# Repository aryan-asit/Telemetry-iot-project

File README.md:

# 4-Layer IoT Telemetry Board

A custom 4-layer IoT Telemetry Board designed from scratch using KiCad. The board is built around an ESP32 and integrates environmental sensing, local data storage, USB connectivity, wireless communication, and battery charging and power management in a compact PCB.

## Project Overview

The goal of this project was to design a compact and reliable IoT hardware platform capable of collecting environmental data, processing it locally, storing telemetry data, and communicating wirelessly.

The project covers the complete PCB development workflow, from component selection and schematic design to PCB layout, verification, 3D inspection, and manufacturing file generation.

## 3D PCB View

## Key Features

### ESP32 Processing and Connectivity

The ESP32 is the main controller of the board and provides:

- Sensor data acquisition
- Local data processing
- Wi-Fi connectivity
- Bluetooth connectivity
- Communication with external peripherals

### Sensors

The board includes multiple sensing elements for environmental and acoustic monitoring:

- Microphone for sound sensing
- Humidity sensor for environmental monitoring
- Ambient light sensor for light-level measurement

### Data Storage

Two storage options are integrated into the board:

- Micro SD card for removable and higher-capacity data storage
- Flash memory for local non-volatile storage

### Power Management

The power section is based on the MCP73871 battery charging and power-management IC.

Main power features include:

- USB Type-C power input
- Battery charging
- Power-path management
- Battery-powered operation
- Dedicated 3.3 V regulation using an LM1117-3.3V regulator

### USB Type-C

A USB Type-C connector is included for power input and USB communication.

## PCB Stack-Up

The board uses a 4-layer PCB stack-up to improve power distribution, grounding, and routing flexibility.

| Layer | Purpose |
|---|---|
| Layer 1 | Signal |
| Layer 2 | Ground Plane |
| Layer 3 | Power Plane - 5 V and 3.3 V zones |
| Layer 4 | Signal |

The dedicated ground and power layers provide continuous return paths and simplify power distribution across the board.

## Communication Interfaces

| Interface | Purpose |
|---|---|
| I2C | Sensor and peripheral communication |
| SPI | SD card, flash memory, and other peripherals |
| USB | Power, programming, and communication |
| Wi-Fi | Wireless connectivity |
| Bluetooth | Short-range wireless connectivity |

## System Architecture

```text
                         +---------------------+
                         |     USB Type-C      |
                         |    Power / USB      |
                         +----------+----------+
                                    |
                                    v
                         +---------------------+
                         |      MCP73871       |
                         | Battery Charging &  |
                         |   Power Management  |
                         +----------+----------+
                                    |
                                    v
                         +---------------------+
                         |     LM1117-3.3V     |
                         |  Voltage Regulation |
                         +----------+----------+
                                    |
                                    v
                    +------------------------------+
                    |             ESP32            |
                    |      Processing & Control    |
                    |                              |
                    |       Wi-Fi + Bluetooth     |
                    +--------+----------+----------+
                             |          |
                 +-----------+----------+-----------+
                 |                      |           |
                 v                      v           v
          +-------------+       +-------------+ +---------+
          |   Sensors   |       |   Storage   | |  USB    |
          |             |       |             | | Type-C  |
          | Microphone  |       | Micro SD    | |         |
          | Humidity    |       | Flash       | |         |
          | Light       |       |             | |         |
          +-------------+       +-------------+ +---------+
```

## PCB Design Workflow

### 1. Concept Development

Defined the requirements for a compact IoT telemetry platform covering sensing, processing, storage, communication, and power management.

### 2. Component Selection

Selected the ESP32, sensors, memory devices, charging IC, regulator, connectors, and supporting components based on the system requirements.

### 3. Schematic Design

Designed and reviewed the complete circuit schematic and connected the individual functional blocks.

### 4. Footprint Selection and Creation

Selected suitable KiCad footprints and created or customized footprints where required.

### 5. PCB Layout

Defined the 4-layer stack-up and placed components while considering board size, routing complexity, signal paths, power distribution, and component accessibility.

### 6. Routing

Routed signal, power, and communication connections with attention to return paths, grounding, and clean power distribution.

### 7. 3D Verification

Configured 3D models and inspected the complete board to verify component placement and the overall physical arrangement.

### 8. ERC and DRC Verification

Performed Electrical Rules Check (ERC) and Design Rules Check (DRC) to identify and resolve schematic and PCB design issues.

### 9. Manufacturing Output

Generated Gerber and other required manufacturing files for PCB fabrication.

## Design Highlights

### 4-Layer PCB Design

The dedicated ground and power layers provide better power distribution and more flexible signal routing than a basic 2-layer approach.

### Integrated Power Management

The MCP73871 handles battery charging and power-path management, while the LM1117-3.3V provides a regulated 3.3 V supply for the low-voltage circuitry.

### Multiple Peripheral Interfaces

The board combines sensors, storage, USB, and wireless communication on a single PCB, making it suitable for different embedded and IoT applications.

### Compact Functional Layout

The component placement and routing were optimized to balance board size, functionality, accessibility, and routing complexity.

## Repository Contents

```text
Telemetry-iot-project/
|
+-- IOT_PCB/
|   +-- KiCad schematic and PCB design files
|
+-- images/
|   +-- telemetry-board-3d.png
|
+-- schematic files.pdf
|   +-- Complete schematic documentation
|
+-- Screenshot *.png
|   +-- PCB design and layout screenshots
|
+-- README.md
|   +-- Project documentation
```

## Tools and Technologies

### Hardware

- ESP32
- Microphone
- Humidity sensor
- Ambient light sensor
- Micro SD card
- Flash memory
- MCP73871
- LM1117-3.3V
- USB Type-C

### PCB Design

- KiCad v10
- Schematic Capture
- PCB Layout
- Footprint and Symbol Management
- 3D PCB Visualization
- ERC
- DRC
- Gerber Generation

### Communication

- I2C
- SPI
- USB
- Wi-Fi
- Bluetooth

## Applications

The board can be adapted for applications such as:

- Environmental monitoring
- IoT sensor nodes
- Wireless telemetry
- Data logging
- Noise monitoring
- Ambient light monitoring
- Smart embedded systems
- Battery-powered IoT devices
- Hardware prototyping

## What I Learned

This project provided practical experience in:

- 4-layer PCB design
- Schematic design and verification
- Component selection
- Footprint management
- PCB placement and routing
- Power distribution and grounding
- Signal-integrity considerations
- ERC and DRC debugging
- 3D PCB inspection
- Gerber generation
- Iterative hardware design and debugging

One of the main design challenges was finding the right balance between board size, routing complexity, power distribution, component placement, and overall functionality.

## Future Improvements

Possible future improvements include:

- Additional environmental sensors
- Cloud-based telemetry
- OTA firmware updates
- Improved power optimization
- Additional communication interfaces
- Dedicated debugging and programming features
- Enclosure and mechanical integration
- Web or mobile dashboard for telemetry visualization

## Author

**Aryan Asit**  
B.Tech - Electronics and Communication Engineering  
VLSI and Embedded Systems  
Indian Institute of Information Technology Manipur

## Repository

GitHub: https://github.com/aryan-asit/Telemetry-iot-project

## License

Refer to the repository license for usage and redistribution terms.

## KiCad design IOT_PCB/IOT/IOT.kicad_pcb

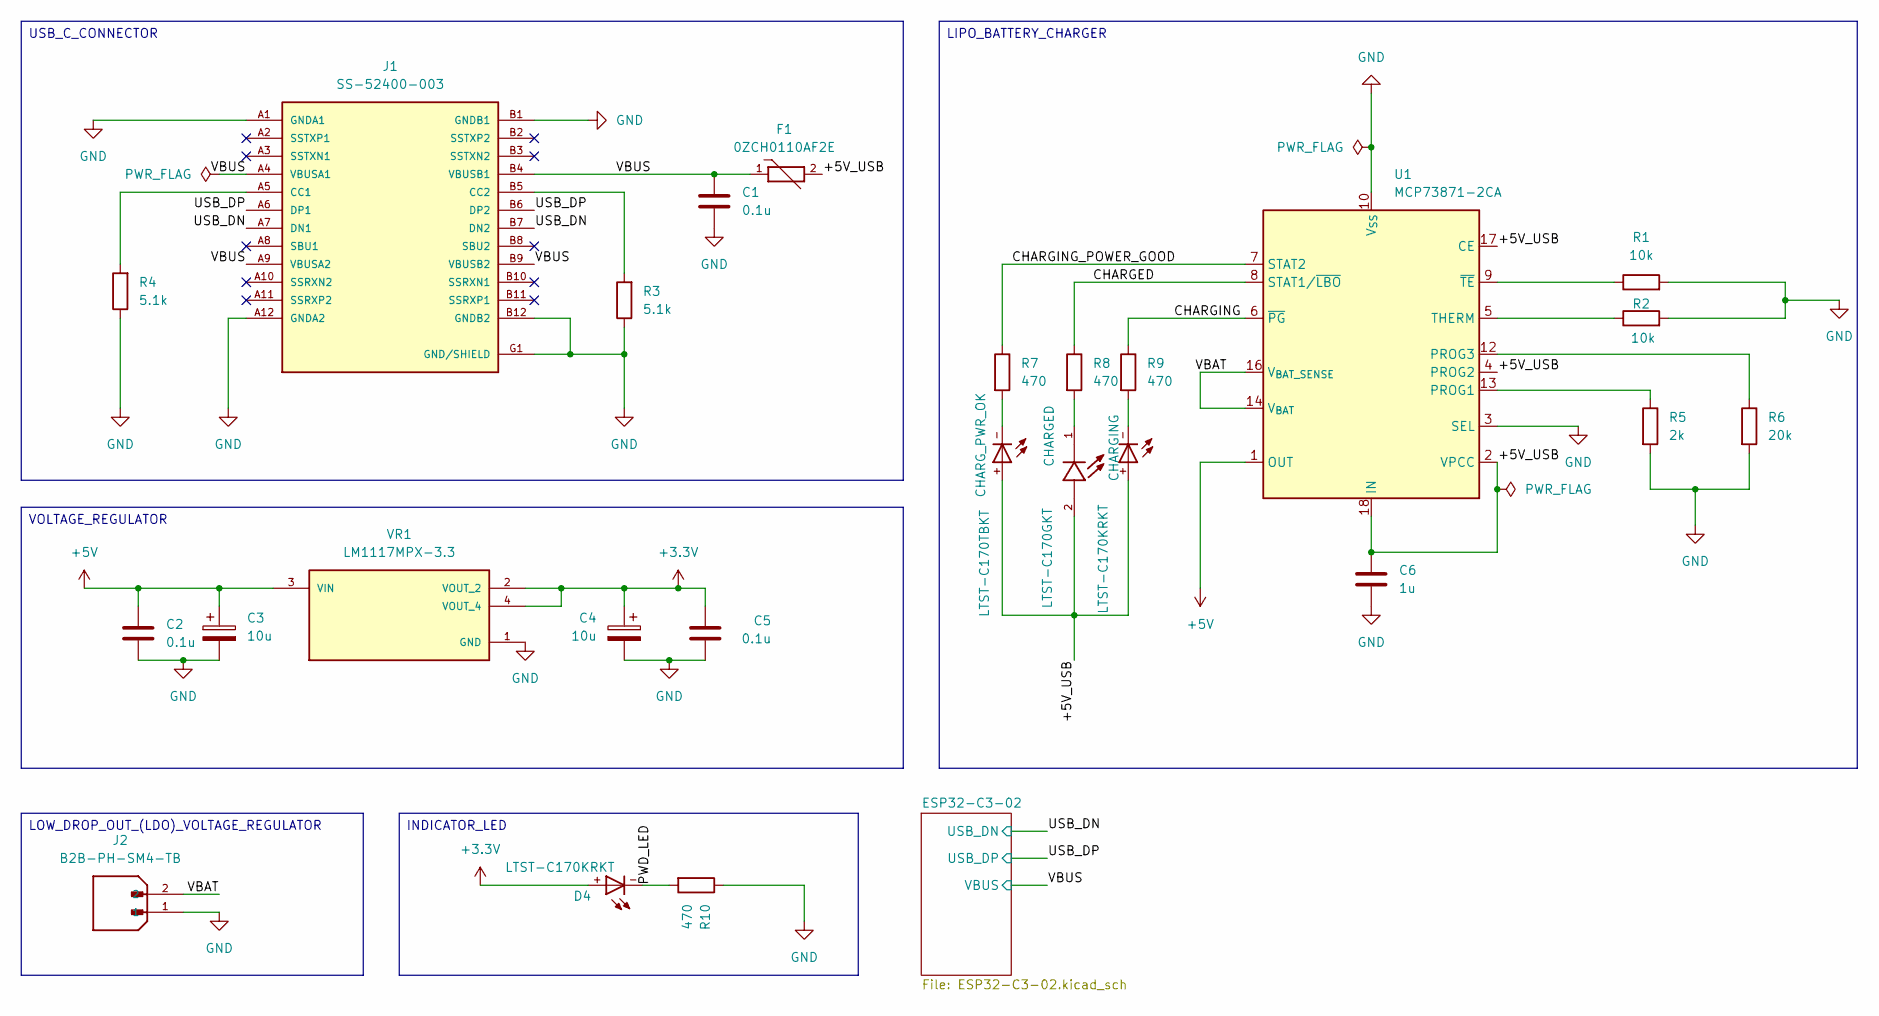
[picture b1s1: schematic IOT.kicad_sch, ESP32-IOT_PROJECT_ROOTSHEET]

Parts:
C1, C2, C5: 0.1u; C_0805_2012Metric
C3, C4: 10u; T491A
C6: 1u; C_0805_2012Metric
CHARGED: LTST-C170GKT; LED_LTST-C170GKT; PARTREV I
CHARGING: LTST-C170KRKT; DIOC200X125X110
CHARG_PWR_OK: LTST-C170TBKT; DIOC200X125X110
D4: LTST-C170KRKT; DIOC200X125X110
F1: 0ZCH0110AF2E; FUSC3225X100N; PARTREV Apr2023
J1: SS-52400-003; BELFUSE_SS-52400-003; PARTREV A0
J2: B2B-PH-SM4-TB; JST_B2B-PH-SM4-TB; PARTREV N/A
R1, R2: 10k; R_0805_2012Metric
R3, R4: 5.1k; R_0805_2012Metric
R5: 2k; R_0805_2012Metric
R6: 20k; R_0805_2012Metric
R7, R8, R9, R10: 470; R_0805_2012Metric
U1: MCP73871-2CA; QFN-20-1EP_4x4mm_P0.5mm_EP2.5x2.5mm
VR1: LM1117MPX-3.3; VREG_LM1117MPX-3.3; PARTREV O

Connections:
+3.3V: C4.1, C5.1, D4.+, VR1.2 (VOUT_2), VR1.4 (VOUT_4); also elsewhere on the board
+5V: C2.1, C3.1, U1.1 (OUT), U1.20 (OUT), VR1.3 (VIN)
/+5V_USB: C6.1, CHARGED.2, CHARGING.+, CHARG_PWR_OK.+, F1.2, U1.2 (VPCC), U1.4 (PROG2), U1.17 (CE), U1.18 (IN), U1.19 (IN); also elsewhere on the board
/CHARGED: R8.1, U1.8 (STAT1/~LBO)
/CHARGING: R9.1, U1.6 (~PG)
/CHARGING_POWER_GOOD: R7.1, U1.7 (STAT2)
/PWD_LED: D4.-, R10.2
/USB_DN: J1.A7 (DN1), J1.B7 (DN2); also elsewhere on the board
/USB_DP: J1.A6 (DP1), J1.B6 (DP2); also elsewhere on the board
/VBAT: J2.2, U1.14 (V_{BAT}), U1.15 (V_{BAT}), U1.16 (V_{BAT_SENSE})
/VBUS: C1.1, F1.1, J1.A4 (VBUSA1), J1.A9 (VBUSA2), J1.B4 (VBUSB1), J1.B9 (VBUSB2); also elsewhere on the board
GND: C1.2, C2.2, C3.2, C4.2, C5.2, C6.2, J1.A1 (GNDA1), J1.A12 (GNDA2), J1.B1 (GNDB1), J1.B12 (GNDB2), J1.G1 (GND/SHIELD), J1.G2 (GND/SHIELD), J1.G3 (GND/SHIELD), J1.G4 (GND/SHIELD), J1.S1 (GND/SHIELD), J1.S2 (GND/SHIELD), J1.S3 (GND/SHIELD), J1.S4 (GND/SHIELD), J2.1, R1.2, R2.2, R3.1, R4.1, R5.2, R6.2, R10.1, U1.3 (SEL), U1.10 (V_{SS}), U1.11 (V_{SS}), U1.21 (V_{SS}), VR1.1 (GND); also elsewhere on the board
unnamed: CHARGED.1, R8.2
unnamed 36: CHARG_PWR_OK.-, R7.2; also elsewhere on the board
unnamed: CHARGING.-, R9.2
unnamed: J1.A5 (CC1), R4.2
unnamed: J1.B5 (CC2), R3.2
unnamed: R5.1, U1.13 (PROG1)
unnamed: R6.1, U1.12 (PROG3)
unnamed: R2.1, U1.5 (THERM)
unnamed: R1.1, U1.9 (~TE)

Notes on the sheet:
USB_C_CONNECTOR
VOLTAGE_REGULATOR
LIPO_BATTERY_CHARGER
LOW_DROP_OUT_(LDO)_VOLTAGE_REGULATOR
INDICATOR_LED

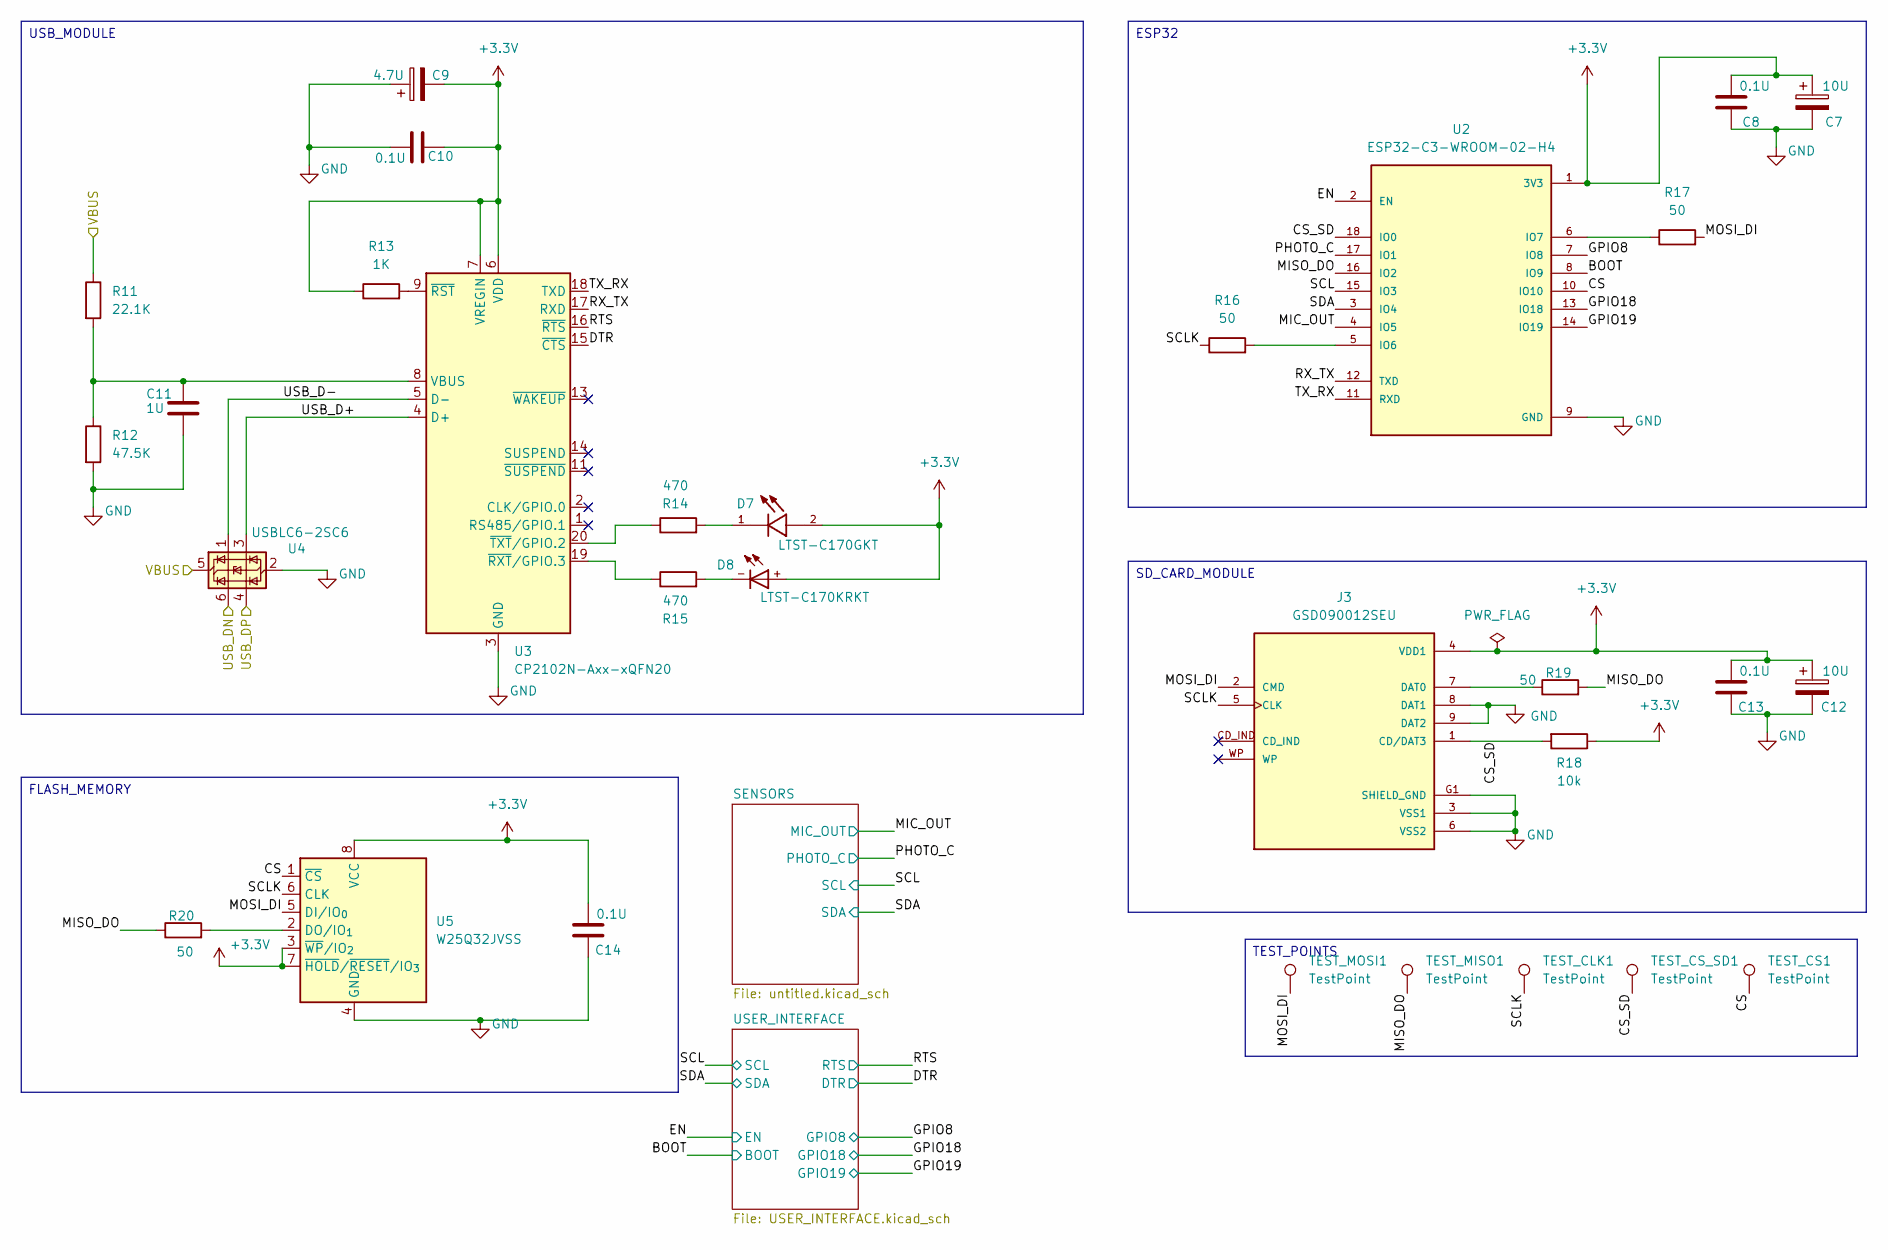
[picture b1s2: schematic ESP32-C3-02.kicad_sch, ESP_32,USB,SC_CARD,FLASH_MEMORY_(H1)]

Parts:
C7, C12: 10U; T491A
C8, C10, C13, C14: 0.1U; C_0805_2012Metric
C9: 4.7U; T491A
C11: 1U; C_0805_2012Metric
D7: LTST-C170GKT; LED_LTST-C170GKT; PARTREV I
D8: LTST-C170KRKT; DIOC200X125X110
J3: GSD090012SEU; AMPHENOL_GSD090012SEU; PARTREV E
R11: 22.1K; R_0805_2012Metric
R12: 47.5K; R_0805_2012Metric
R13: 1K; R_0805_2012Metric
R14, R15: 470; R_0805_2012Metric
R16, R17, R19, R20: 50; R_0805_2012Metric
R18: 10k; R_0805_2012Metric
TEST_CLK1: TestPoint; TestPoint_Pad_D1.0mm
TEST_CS1: TestPoint; TestPoint_Pad_D1.0mm
TEST_CS_SD1: TestPoint; TestPoint_Pad_D1.0mm
TEST_MISO1: TestPoint; TestPoint_Pad_D1.0mm
TEST_MOSI1: TestPoint; TestPoint_Pad_D1.0mm
U2: ESP32-C3-WROOM-02-H4; MODULE_ESP32-C3-WROOM-02-H4
U3: CP2102N-Axx-xQFN20; SiliconLabs_QFN-20-1EP_3x3mm_P0.5mm_EP1.8x1.8mm
U4: USBLC6-2SC6; SOT-23-6
U5: W25Q32JVSS; SOIC-8_5.3x5.3mm_P1.27mm

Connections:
+3.3V: C7.1, C8.1, C9.2, C10.2, C12.1, C13.1, C14.1, D7.2, D8.+, J3.4 (VDD1), R13.1, R18.1, U2.1 (3V3), U3.6 (VDD), U3.7 (VREGIN), U5.3 (~WP/IO_{2}), U5.7 (~HOLD/~RESET/IO_{3}), U5.8 (VCC); also elsewhere on the board
/ESP32-C3-02/BOOT: U2.8 (IO9); also elsewhere on the board
/ESP32-C3-02/CS: TEST_CS1.1 (1_1), U2.10 (IO10), U5.1 (~CS)
/ESP32-C3-02/CS_SD: J3.1 (CD/DAT3), R18.2, TEST_CS_SD1.1 (1_1), U2.18 (IO0)
/ESP32-C3-02/DTR: U3.15 (~CTS); also elsewhere on the board
/ESP32-C3-02/EN: U2.2 (EN); also elsewhere on the board
/ESP32-C3-02/GPIO8: U2.7 (IO8); also elsewhere on the board
/ESP32-C3-02/GPIO18: U2.13 (IO18); also elsewhere on the board
/ESP32-C3-02/GPIO19: U2.14 (IO19); also elsewhere on the board
/ESP32-C3-02/MIC_OUT: U2.4 (IO5); also elsewhere on the board
/ESP32-C3-02/MISO_DO: R19.2, R20.1, TEST_MISO1.1 (1_1), U2.16 (IO2)
/ESP32-C3-02/MOSI_DI: J3.2 (CMD), R17.2, TEST_MOSI1.1 (1_1), U5.5 (DI/IO_{0})
/ESP32-C3-02/PHOTO_C: U2.17 (IO1); also elsewhere on the board
/ESP32-C3-02/RTS: U3.16 (~RTS); also elsewhere on the board
/ESP32-C3-02/RX_TX: U2.12 (TXD), U3.17 (RXD)
/ESP32-C3-02/SCL: U2.15 (IO3); also elsewhere on the board
/ESP32-C3-02/SCLK: J3.5 (CLK), R16.1, TEST_CLK1.1 (1_1), U5.6 (CLK)
/ESP32-C3-02/SDA: U2.3 (IO4); also elsewhere on the board
/ESP32-C3-02/TX_RX: U2.11 (RXD), U3.18 (TXD)
/ESP32-C3-02/USB_D+: U3.4 (D+), U4.3 (I/O2)
/ESP32-C3-02/USB_D-: U3.5 (D-), U4.1 (I/O1)
/USB_DN: U4.6 (I/O1); also elsewhere on the board
/USB_DP: U4.4 (I/O2); also elsewhere on the board
/VBUS: R11.1, U4.5 (VBUS); also elsewhere on the board
GND: C7.2, C8.2, C9.1, C10.1, C11.2, C12.2, C13.2, C14.2, J3.3 (VSS1), J3.6 (VSS2), J3.8 (DAT1), J3.9 (DAT2), J3.G1 (SHIELD_GND), J3.G2 (SHIELD_GND), J3.G3 (SHIELD_GND), J3.G4 (SHIELD_GND), R12.2, U2.9 (GND), U2.19 (GND), U2.20 (GND), U2.21 (GND), U2.22 (GND), U2.23 (GND), U2.24 (GND), U2.25 (GND), U2.26 (GND), U2.27 (GND), U2.28 (GND), U2.29 (GND), U2.30 (GND), U2.31 (GND), U2.32 (GND), U2.33 (GND), U2.34 (GND), U2.35 (GND), U2.36 (GND), U2.37 (GND), U2.38 (GND), U2.39 (GND), U3.3 (GND), U3.12 (GND), U3.21 (GND), U4.2 (GND), U5.4 (GND); also elsewhere on the board
unnamed: D7.1, R14.2
unnamed: D8.-, R15.2
unnamed: J3.7 (DAT0), R19.1
unnamed: R16.2, U2.5 (IO6)
unnamed: R17.1, U2.6 (IO7)
unnamed: C11.1, R11.2, R12.1, U3.8 (VBUS)
unnamed: R13.2, U3.9 (~RST)
unnamed: R15.1, U3.19 (~RXT/GPIO.3)
unnamed: R14.1, U3.20 (~TXT/GPIO.2)
unnamed: R20.2, U5.2 (DO/IO_{1})

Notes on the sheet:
USB_MODULE
FLASH_MEMORY
SD_CARD_MODULE
TEST_POINTS
ESP32

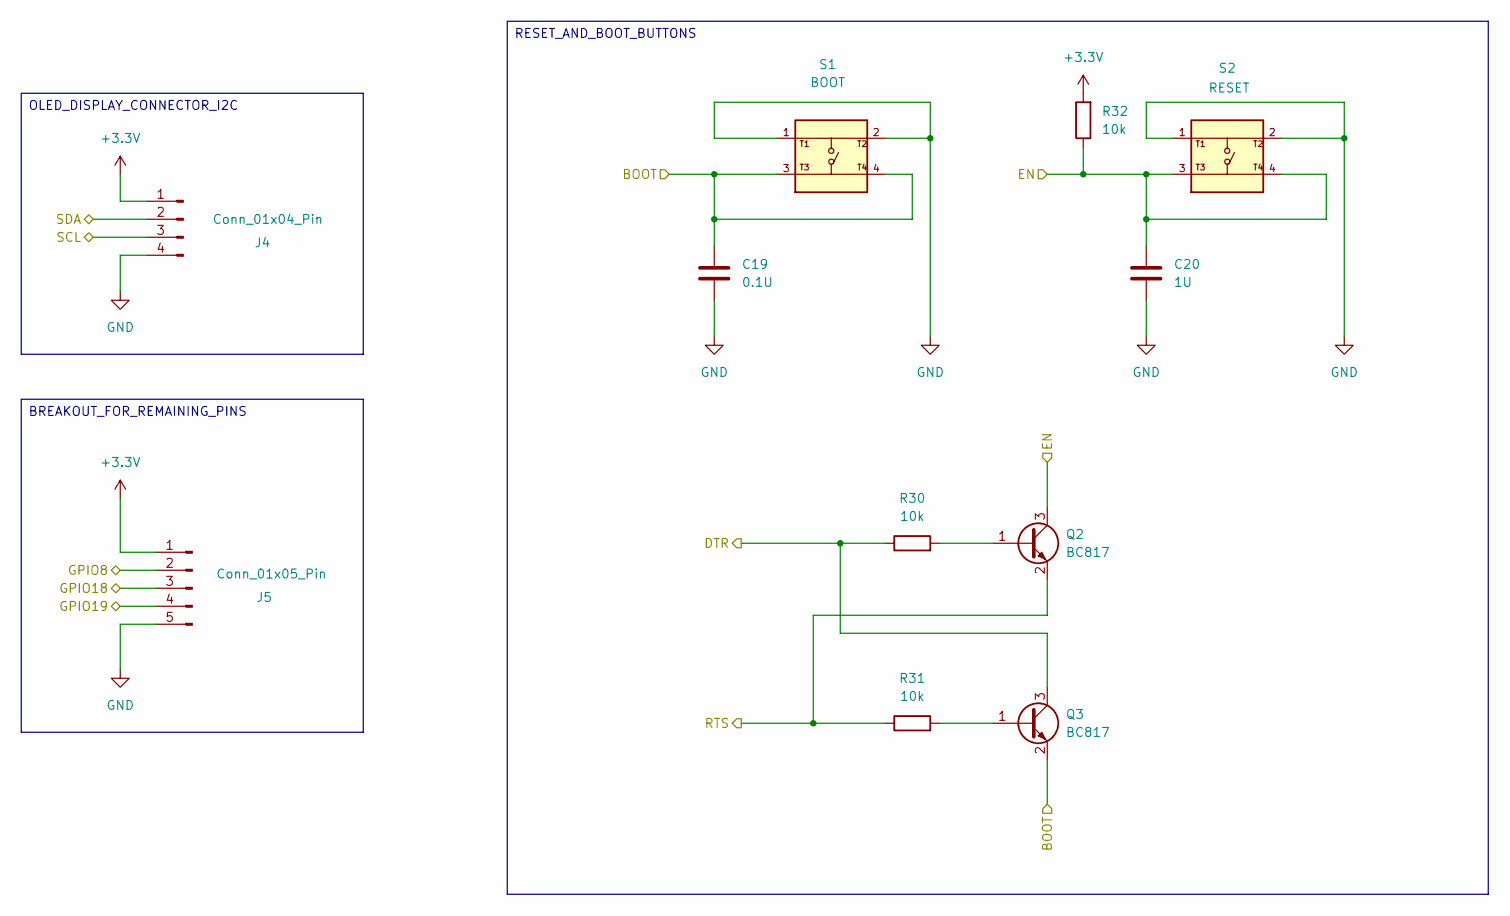
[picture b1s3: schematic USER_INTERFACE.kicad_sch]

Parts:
C19: 0.1U; C_0805_2012Metric
C20: 1U; C_0805_2012Metric
J4: Conn_01x04_Pin; PinHeader_1x04_P2.54mm_Vertical
J5: Conn_01x05_Pin; PinHeader_1x05_P2.54mm_Vertical
Q2, Q3: BC817; SOT-23
R30, R31, R32: 10k; R_0805_2012Metric
S1: BOOT; SW_USLPT2819DT2TR; PARTREV P
S2: RESET; SW_USLPT2819DT2TR; PARTREV P

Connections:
+3.3V: J4.1, J5.1, R32.2; also elsewhere on the board
/ESP32-C3-02/BOOT: C19.1, Q3.2 (E), S1.3, S1.4; also elsewhere on the board
/ESP32-C3-02/DTR: Q3.3 (C), R30.1; also elsewhere on the board
/ESP32-C3-02/EN: C20.1, Q2.3 (C), R32.1, S2.3, S2.4; also elsewhere on the board
/ESP32-C3-02/GPIO8: J5.2; also elsewhere on the board
/ESP32-C3-02/GPIO18: J5.3; also elsewhere on the board
/ESP32-C3-02/GPIO19: J5.4; also elsewhere on the board
/ESP32-C3-02/RTS: Q2.2 (E), R31.1; also elsewhere on the board
/ESP32-C3-02/SCL: J4.3; also elsewhere on the board
/ESP32-C3-02/SDA: J4.2; also elsewhere on the board
GND: C19.2, C20.2, J4.4, J5.5, S1.1, S1.2, S2.1, S2.2; also elsewhere on the board
unnamed: Q2.1 (B), R30.2
unnamed: Q3.1 (B), R31.2

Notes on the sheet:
RESET_AND_BOOT_BUTTONS
BREAKOUT_FOR_REMAINING_PINS
OLED_DISPLAY_CONNECTOR_I2C

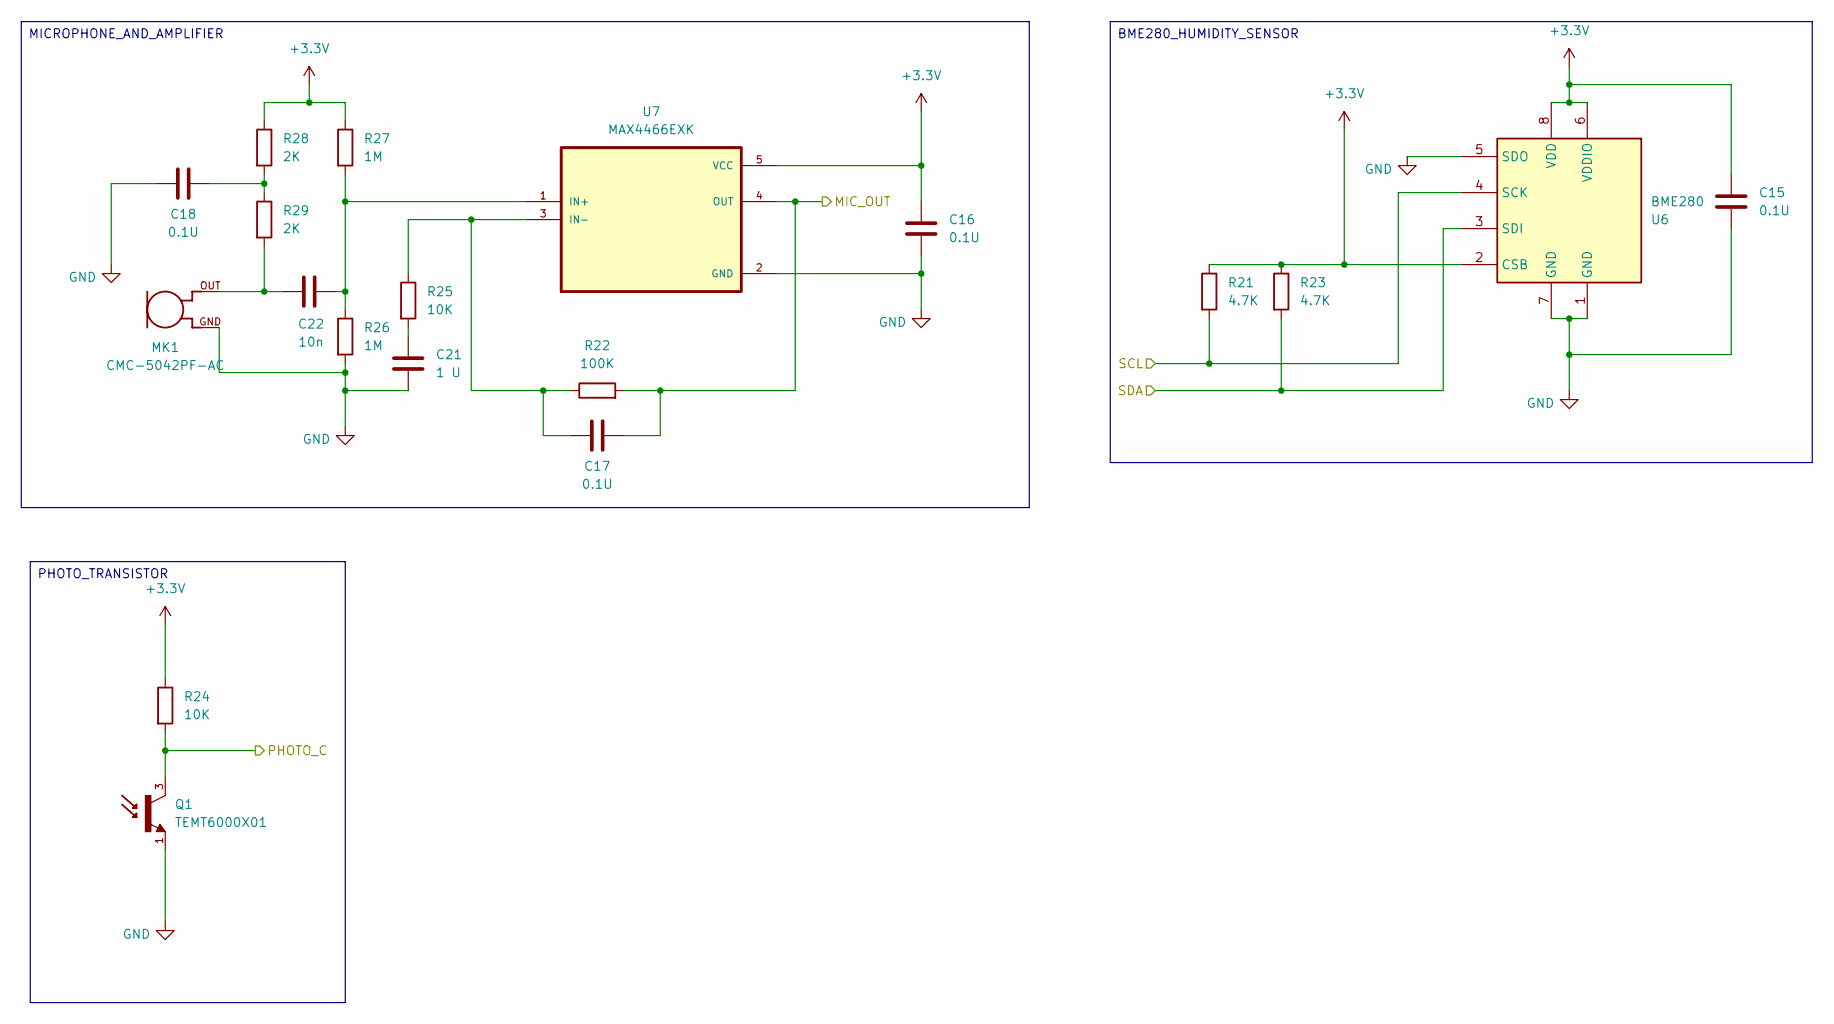
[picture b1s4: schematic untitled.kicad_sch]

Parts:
C15, C16, C17, C18: 0.1U; C_0805_2012Metric
C21: 1 U; C_0805_2012Metric
C22: 10n; C_0805_2012Metric
MK1: CMC-5042PF-AC; CUI_CMC-5042PF-AC
Q1: TEMT6000X01; TRANS_TEMT6000X01; PARTREV 1.9
R21, R23: 4.7K; R_0805_2012Metric
R22: 100K; R_0805_2012Metric
R24, R25: 10K; R_0805_2012Metric
R26, R27: 1M; R_0805_2012Metric
R28, R29: 2K; R_0805_2012Metric
U6: BME280; Bosch_LGA-8_2.5x2.5mm_P0.65mm_ClockwisePinNumbering
U7: MAX4466EXK; SOT65P210X110-5N

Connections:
+3.3V: C15.1, C16.1, R21.1, R23.1, R24.1, R27.1, R28.1, U6.2 (CSB), U6.6 (VDDIO), U6.8 (VDD), U7.5 (VCC); also elsewhere on the board
/ESP32-C3-02/MIC_OUT: C17.2, R22.2, U7.4 (OUT); also elsewhere on the board
/ESP32-C3-02/PHOTO_C: Q1.3, R24.2; also elsewhere on the board
/ESP32-C3-02/SCL: R21.2, U6.4 (SCK); also elsewhere on the board
/ESP32-C3-02/SDA: R23.2, U6.3 (SDI); also elsewhere on the board
GND: C15.2, C16.2, C18.1, C21.2, MK1.GND, Q1.1, R26.2, U6.1 (GND), U6.5 (SDO), U6.7 (GND), U7.2 (GND); also elsewhere on the board
unnamed: C18.2, R28.2, R29.1
unnamed: C21.1, R25.2
unnamed: C22.1, MK1.OUT, R29.2
unnamed: C22.2, R26.1, R27.2, U7.1 (IN+)
unnamed: C17.1, R22.1, R25.1, U7.3 (IN-)

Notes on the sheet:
BME280_HUMIDITY_SENSOR
PHOTO_TRANSISTOR
MICROPHONE_AND_AMPLIFIER

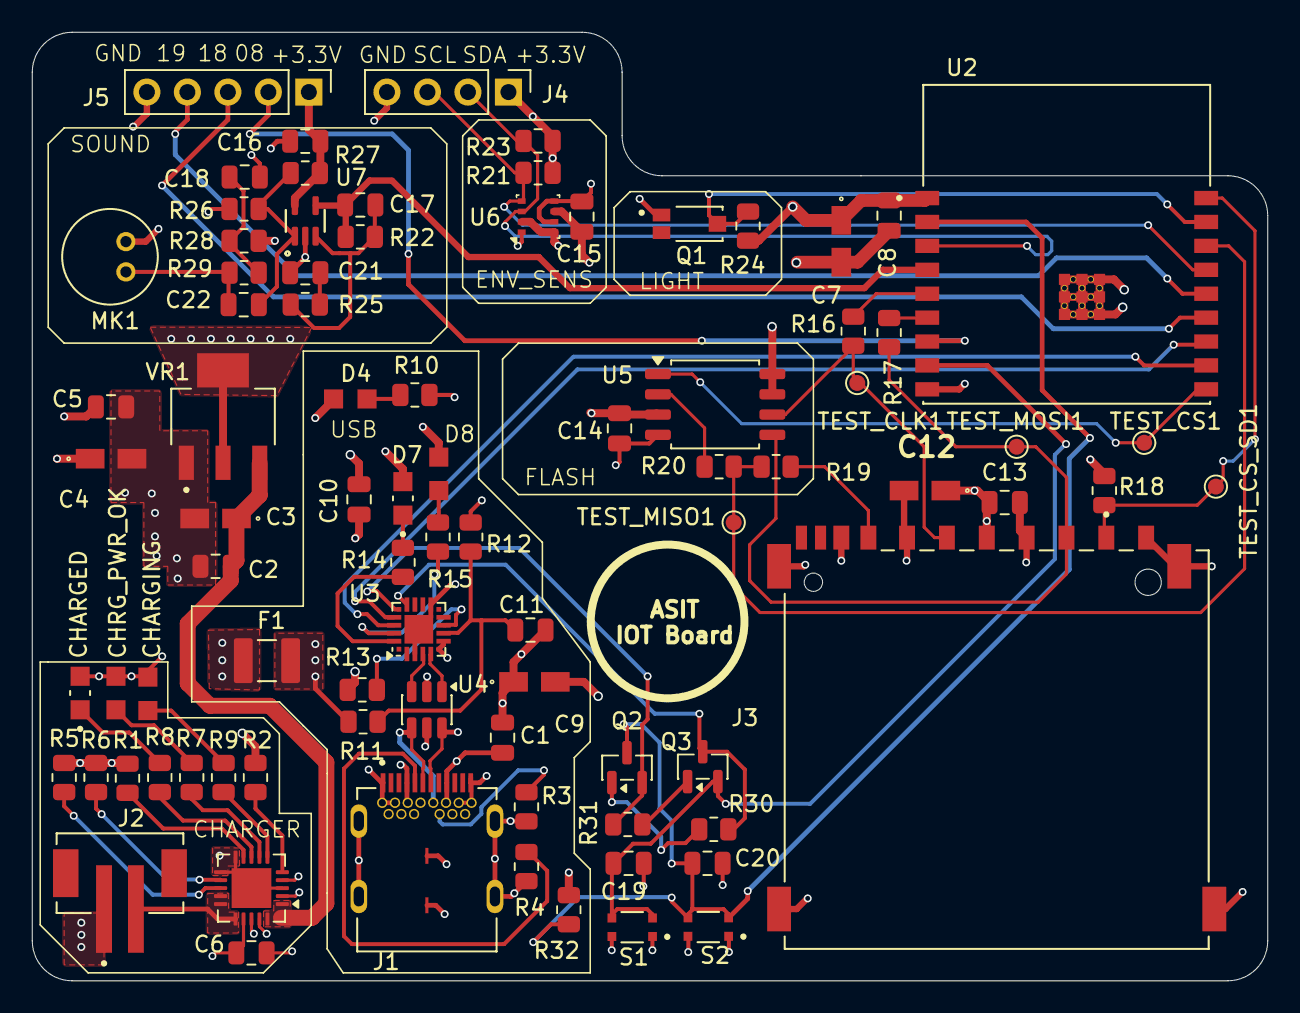
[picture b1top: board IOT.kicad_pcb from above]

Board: 4 copper layers, 77.5 x 59.5 mm, 85 parts (0 on the bottom side), 58 nets.

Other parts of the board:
CHRG_PWR_OK: LTST-C170TBKT; DIOC200X125X110

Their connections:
/+5V_USB: CHRG_PWR_OK.+; also elsewhere on the board
unnamed 36: CHRG_PWR_OK.-; also elsewhere on the board

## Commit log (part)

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2026-06-17 schematic files
    schematic files is uploded
